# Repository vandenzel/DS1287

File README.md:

# DS1287

Information and diagnostics to test the Dallas/Maxim DS1287 and compatible Real-time Clock and CMOS RAM devices, as well as a design to replace them useing a DS12885 chip, a watch crystal and a battery.

## Datasheet:

* https://datasheets.maximintegrated.com/en/ds/DS12885-DS12C887A.pdf

## Code

The _diag_ folder contains an Arduino program that lets a Pro Micro device connect
to a DS1287, or compatible device. It gives access to the first 50 registers of the device (DS1287 compatible) and can be expanded to all 128 registers of a DS12887 compatible device.

### Notes on source files:

The source files are in _diag/src_ and relate to each other as follows. Only the
basename is given, if both a _.cpp_ and a _.h_ file exist, they are related.

* _main_ contains the main Arduino code
* _DS1287_ is the interface to the device, using _Pin_ and _Bus_
* _Pin_ and _Bus_ as a class-based GPIO interface, translating the 
  Arduino _pinMode_ and _digitalRead_-style of interfacing to an interface 
  with less typing.
* _UI_ is a simple command line interface on the serial port, that handles typing
  commands.

## Replacement design

The _DS12887_ folder contains a KiCAD project with a simple design to replace the DS12887 with a DS12885 chip.

The design is neither complete nor tested. At the moment it just looks good on KiCAD's 3D viewer.

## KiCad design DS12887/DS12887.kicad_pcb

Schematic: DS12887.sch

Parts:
BT1: CR1220; BatteryHolder_Keystone_500
C1, C2: 100n; C_1206_3216Metric_Pad1.42x1.75mm_HandSolder
J1, J2: Conn_01x12_Male; PinHeader_1x12_P2.54mm_Vertical
U1: DS12885T+; TQFP-32_7x7mm_P0.8mm
Y1: Crystal; Crystal_C26-LF_D2.1mm_L6.5mm_Horizontal

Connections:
+BATT: BT1.1 (+), C2.1, U1.22
/AD0: J1.4, U1.1
/AD1: J1.5, U1.2
/AD2: J1.6, U1.3
/AD3: J1.7, U1.5
/AD4: J1.8, U1.7
/AD5: J1.9, U1.8
/AD6: J1.10, U1.9
/AD7: J1.11, U1.11
/AS: J2.2, U1.14
/DS: J2.5, U1.18
/MOT: J1.1, U1.29
/R~W: J2.3, U1.16
/SQW: J2.11, U1.26
/X1: U1.30, Y1.2
/X2: U1.31, Y1.1
/~CS: J2.1, U1.13
/~IRQ: J2.7, U1.21
/~RESET: J2.6, U1.19
GND: BT1.2 (-), C1.2, C2.2, J1.12, U1.12, U1.17
VCC: C1.1, J2.12, U1.28

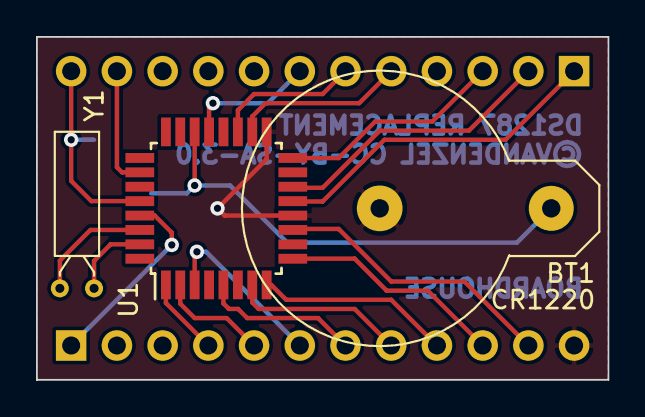
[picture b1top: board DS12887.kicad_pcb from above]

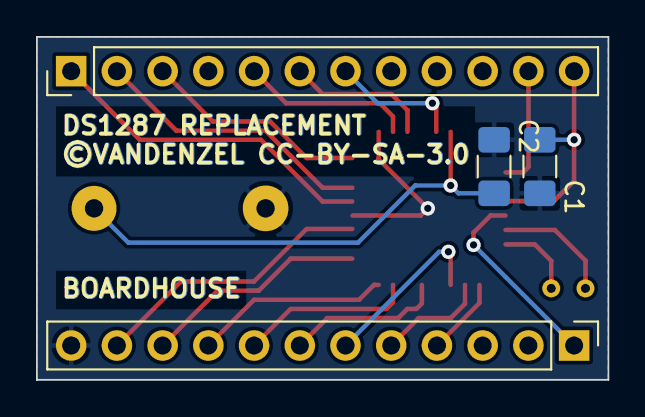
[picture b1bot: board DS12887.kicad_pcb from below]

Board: 2 copper layers, 31.8 x 19.0 mm, 7 parts (4 on the bottom side), 21 nets.

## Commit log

2020-06-23 initial
2020-06-23 created README.md
2021-02-15 added replacement pcb design

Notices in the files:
DS12887/DS12887.kicad_pcb:
©VANDENZEL CC-BY-SA-3.0
